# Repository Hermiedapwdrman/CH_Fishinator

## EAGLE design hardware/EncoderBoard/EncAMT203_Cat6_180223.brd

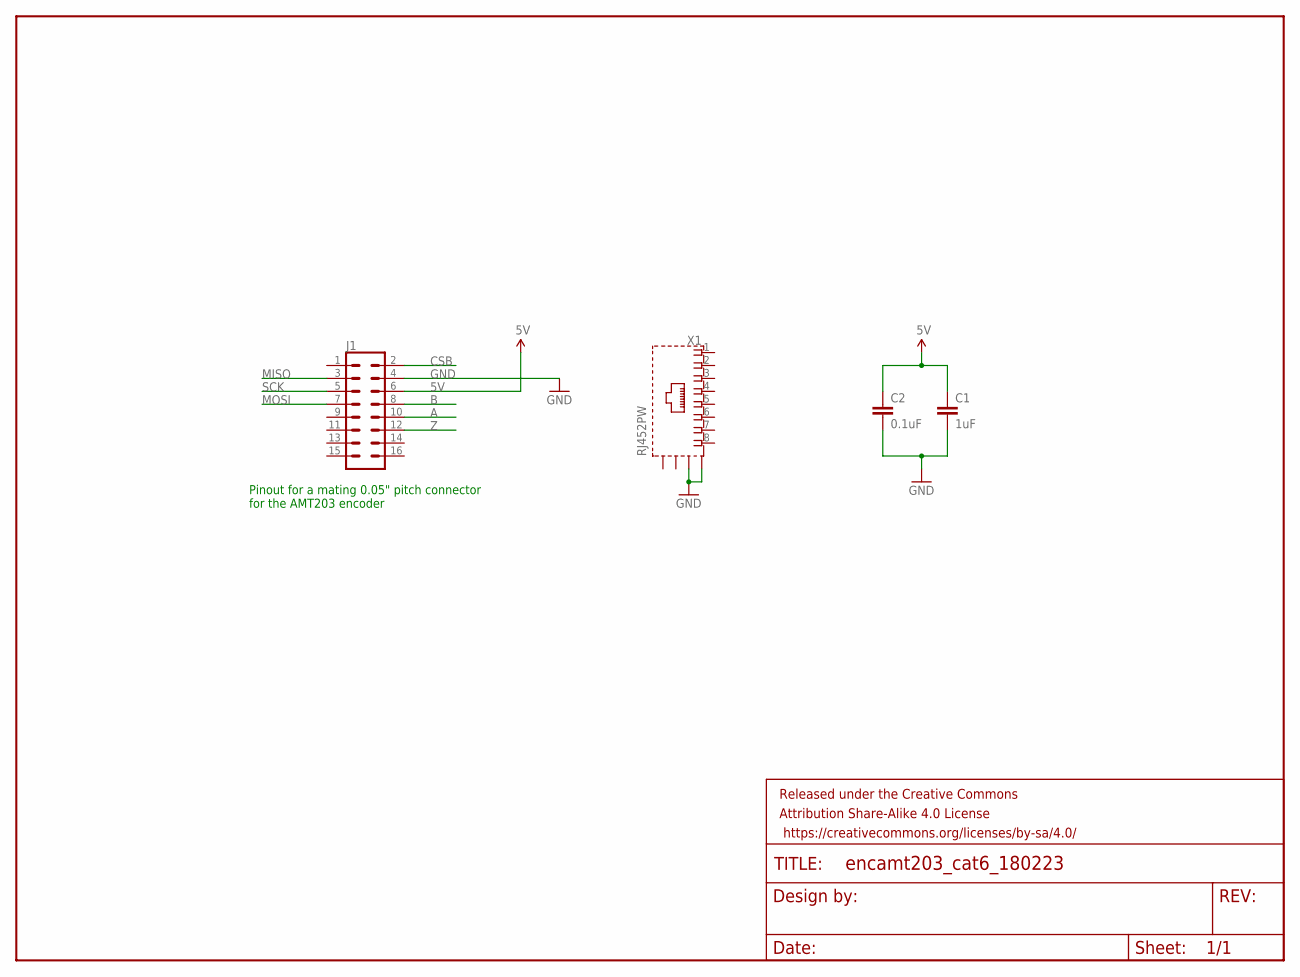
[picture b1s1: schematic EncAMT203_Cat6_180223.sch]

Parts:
C1: 1uF; 0603
C2: 0.1uF; 0603
FRAME1: FRAME-LETTERNO_PACKAGE; DUMMY
J1: CONN_08X2_1.27MM; 2X08_1.27MM
X1: RJ452PW; RJ45-SHIELD1

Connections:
5V: C1.1, C2.1, J1.6
A: J1.10
B: J1.8
CSB: J1.2
GND: C1.2, C2.2, J1.4, X1.S1 (S), X1.S2 (S)
MISO: J1.3
MOSI: J1.7
SCK: J1.5
Z: J1.12

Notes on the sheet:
Pinout for a mating 0.05" pitch connector for the AMT203 encoder

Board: 2 copper layers, 5 parts (3 on the bottom side), 2 nets, no tracks yet.

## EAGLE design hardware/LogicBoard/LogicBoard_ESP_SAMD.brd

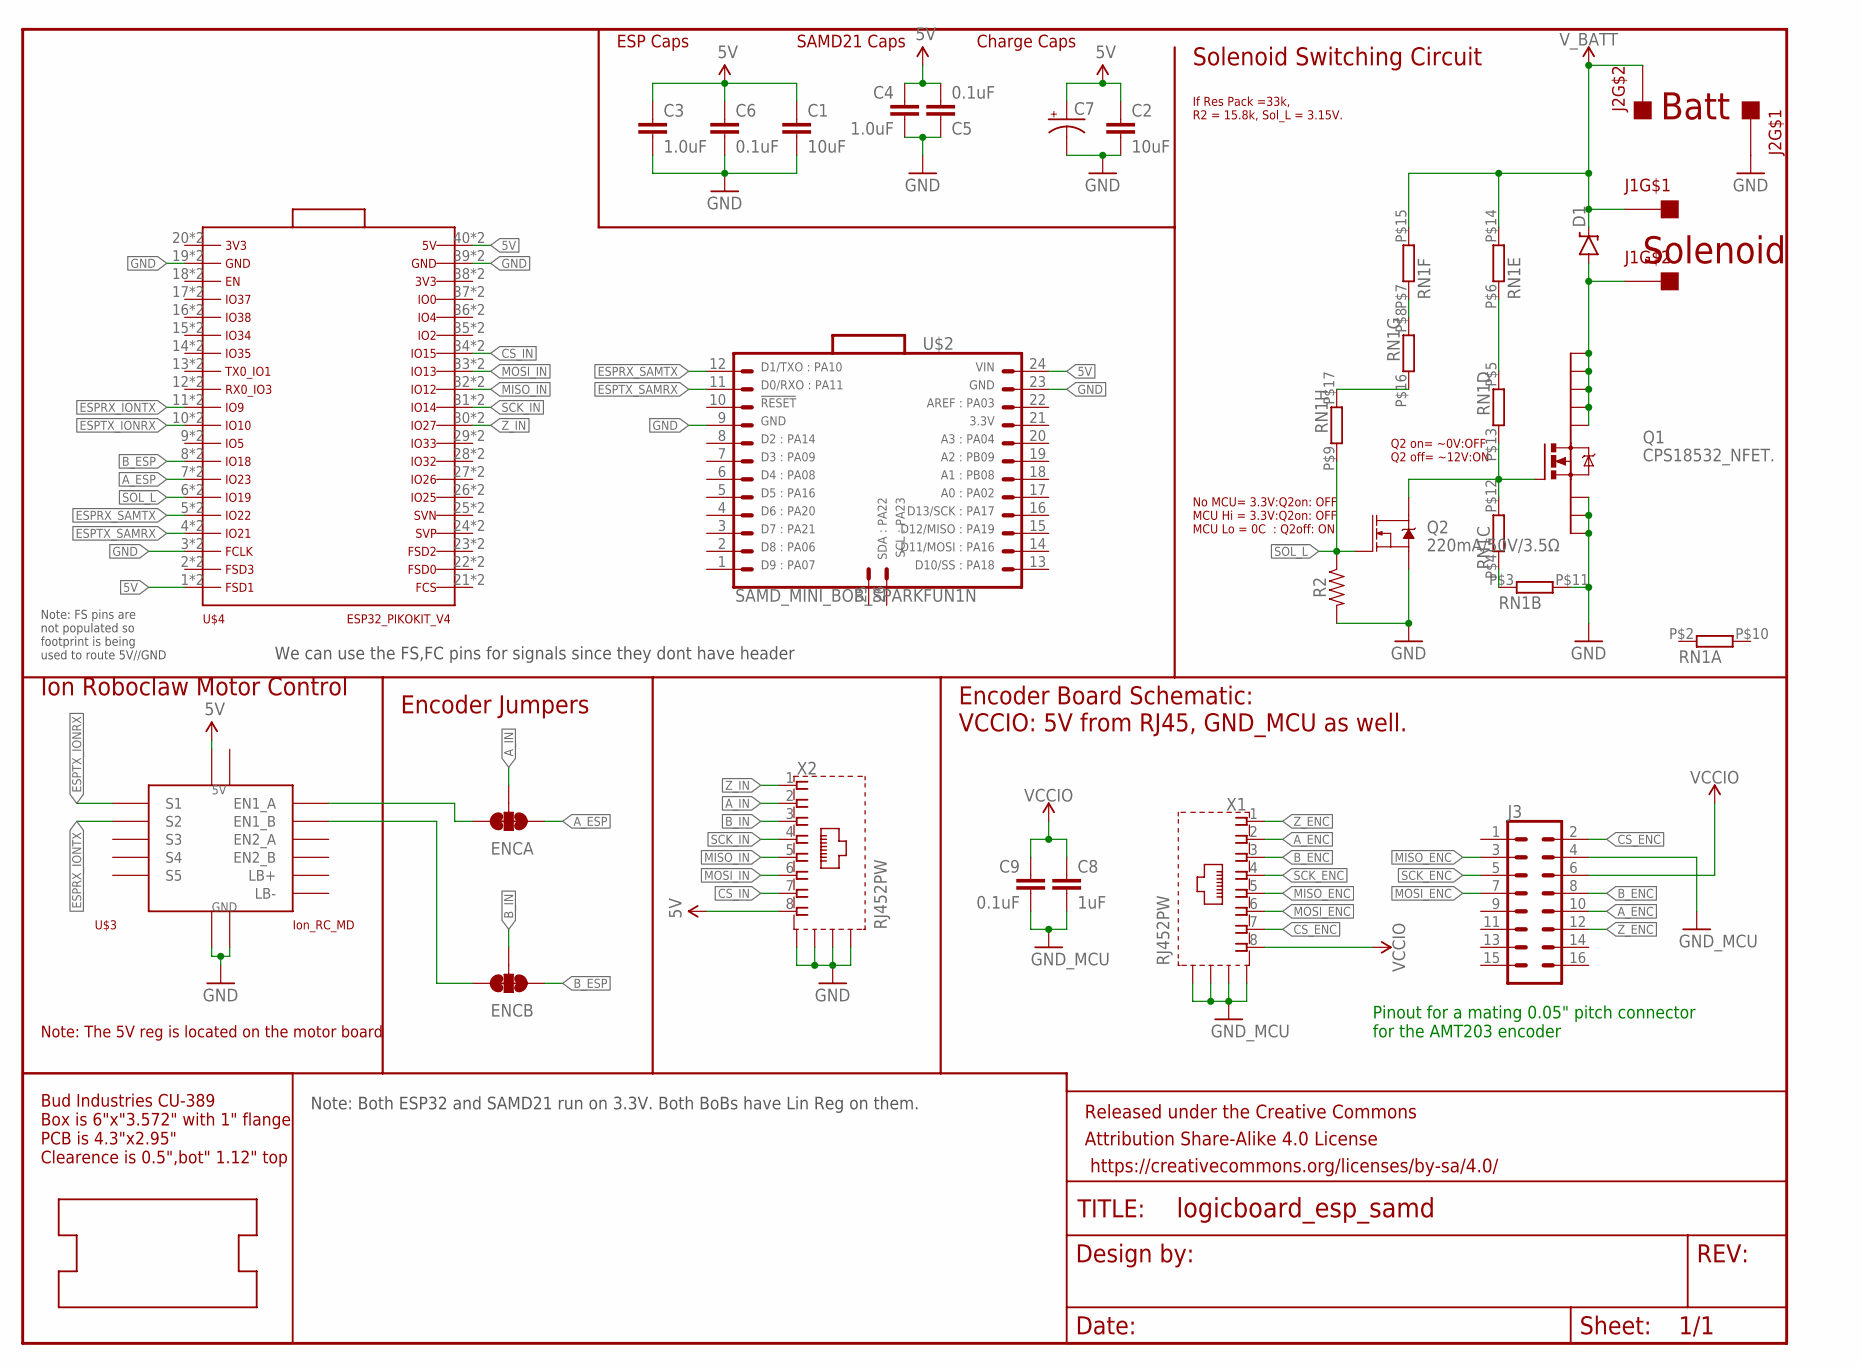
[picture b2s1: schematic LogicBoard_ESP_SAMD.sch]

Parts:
C1, C2: 10uF; 1206
C3, C4: 1.0uF; 0603
C5, C6, C9: 0.1uF; 0603
C7: CAP_POLPTH4; CPOL-RADIAL-1000UF-25V
C8: 1uF; 0603
D1: DIODE-SHOTKEY_SOD-123; SOD-123_MINI-SMA
ENCA: JUMPER-SMT_3_2-NC_TRACE_SILK; SMT-JUMPER_3_2-NC_TRACE_SILK
ENCB: JUMPER-SMT_3_2-NC_TRACE_SILK; SMT-JUMPER_3_2-NC_TRACE_SILK
FRAME1: FRAME-LETTERNO_PACKAGE; DUMMY
J1, J2: M2_TERMINAL_0200SPACING; M2_0200
J3: CONN_08X2_1.27MM; 2X08_1.27MM
Q1: CPS18532_NFET.; CSD18532_NFET_NEXTFET
Q2: 220mA/50V/3.5Ω; SOT23-3
R2: 0603
RN1: RESISTOR-DIL_8R-N742C163; RESISTOR-DIL_742C163
U$1: BOX_BUDIND_CU389STENCIL; BOX_BUDIND_CU389_STENCIL
U$2: SAMD_MINI_BOB_SPARKFUN1N; SAMD_MINI_BOB_SF_NOLABEL
U$3: ION_ROBOCLAW_MOTORDRVTOPVIEW; ION_ROBOCLAW_MOTORCNTL
U$4: ESP32_PICOKIT_V42N; ESP32_PICOKIT_2N
X1, X2: RJ452PW; RJ45-SHIELD1

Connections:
5V: C1.1, C2.1, C3.1, C4.1, C5.2, C6.1, C7.1 (+), U$2.24 (VIN), U$3.5V@1 (5V), U$3.5V@2 (5V), U$3.5V@3 (5V), U$3.5V@4 (5V), U$3.5V@5 (5V), U$4.1, U$4.40, U$4.41, U$4.80, X2.8
!SOL_L!: Q2.1 (G), R2.1, RN1.P$9 (2), U$4.6, U$4.46
A_ENC: J3.10, X1.2
A_ESP: ENCA.1, U$4.7, U$4.47
A_IN: ENCA.2, X2.2
B_ENC: J3.8, X1.3
B_ESP: ENCB.1, U$4.8, U$4.48
B_IN: ENCB.2, X2.3
CS_ENC: J3.2, X1.7
CS_IN: U$4.34, U$4.74, X2.7
ESPRX_IONTX: U$3.S2, U$4.11, U$4.51
ESPRX_SAMTX: U$2.12 (D1), U$4.5, U$4.45
ESPTX_IONRX: U$3.S1, U$4.10, U$4.50
ESPTX_SAMRX: U$2.11 (D0), U$4.4, U$4.44
GND: C1.2, C2.2, C3.2, C4.2, C5.1, C6.2, C7.2 (-), J2.P$2, Q1.P$1 (S1), Q1.P$2 (S2), Q1.P$3 (S3), Q2.2 (S), R2.2, RN1.P$11 (2), U$2.9 (GND), U$2.23 (GND), U$3.GND@1 (GND), U$3.GND@2 (GND), U$3.GND@3 (GND), U$3.GND@4 (GND), U$3.GND@5 (GND), U$3.GND@6 (GND), U$3.GND@7 (GND), U$4.3, U$4.19, U$4.39, U$4.43, U$4.59, U$4.79, X2.S1 (S), X2.S2 (S), X2.S3 (S), X2.S4 (S)
GND_MCU: C8.2, C9.2, J3.4, X1.S1 (S), X1.S2 (S), X1.S3 (S), X1.S4 (S)
MISO_ENC: J3.3, X1.5
MISO_IN: U$4.32, U$4.72, X2.5
MOSI_ENC: J3.7, X1.6
MOSI_IN: U$4.33, U$4.73, X2.6
unnamed: D1.A, J1.P$3, Q1.P$5 (D1), Q1.P$6 (D2), Q1.P$7 (D3), Q1.P$8 (D4), Q1.P$9 (D_PAD)
unnamed: RN1.P$3 (1), RN1.P$4 (1)
unnamed: Q1.P$4 (G), Q2.3 (D), RN1.P$12 (2), RN1.P$13 (2)
unnamed: RN1.P$7 (1), RN1.P$8 (1)
unnamed: RN1.P$16 (2), RN1.P$17 (1)
unnamed: RN1.P$5 (1), RN1.P$6 (1)
unnamed: ENCB.3, U$3.EN1_B
unnamed: ENCA.3, U$3.EN1_A
SCK_ENC: J3.5, X1.4
SCK_IN: U$4.31, U$4.71, X2.4
VCCIO: C8.1, C9.1, J3.6, X1.8
V_BATT: D1.C, J1.P$2, J2.P$3, RN1.P$14 (2), RN1.P$15 (2)
Z_ENC: J3.12, X1.1
Z_IN: U$4.30, U$4.70, X2.1

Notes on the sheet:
Note: Both ESP32 and SAMD21 run on 3.3V. Both BoBs have Lin Reg on them.
We can use the FS,FC pins for signals since they dont have header
Pinout for a mating 0.05" pitch connector for the AMT203 encoder
Encoder Board Schematic: VCCIO: 5V from RJ45, GND_MCU as well.
If Res Pack =33k, R2 = 15.8k, Sol_L = 3.15V.
Encoder Jumpers
Ion Roboclaw Motor Control
Note: The 5V reg is located on the motor board
Solenoid Switching Circuit
Solenoid
Batt
Q2 on= ~0V:OFF Q2 off= ~12V:ON
No MCU= 3.3V:Q2on: OFF MCU Hi = 3.3V:Q2on: OFF MCU Lo = 0C : Q2off: ON
ESP Caps
SAMD21 Caps
Charge Caps
Note: FS pins are not populated so footprint is being used to route 5V//GND

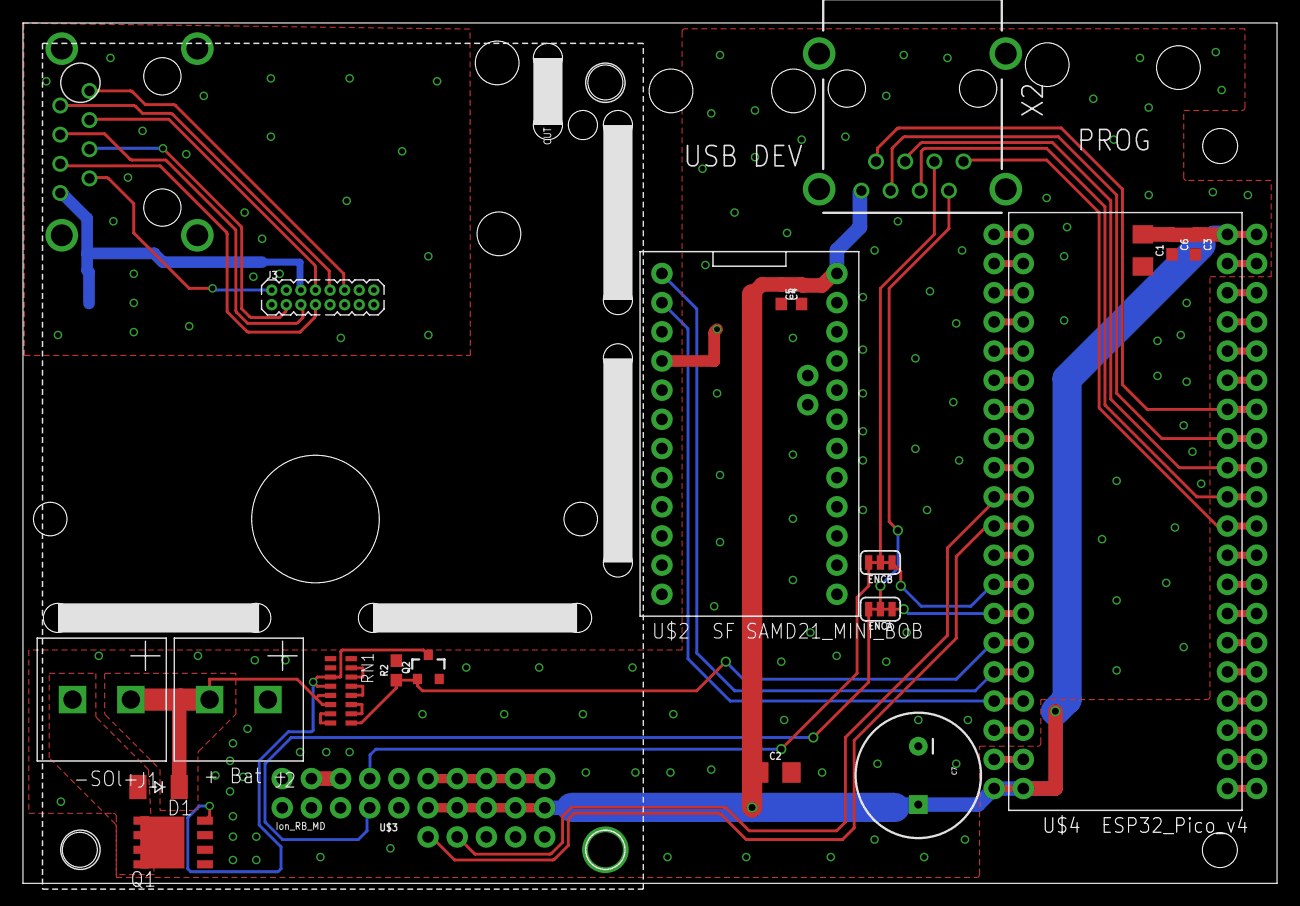
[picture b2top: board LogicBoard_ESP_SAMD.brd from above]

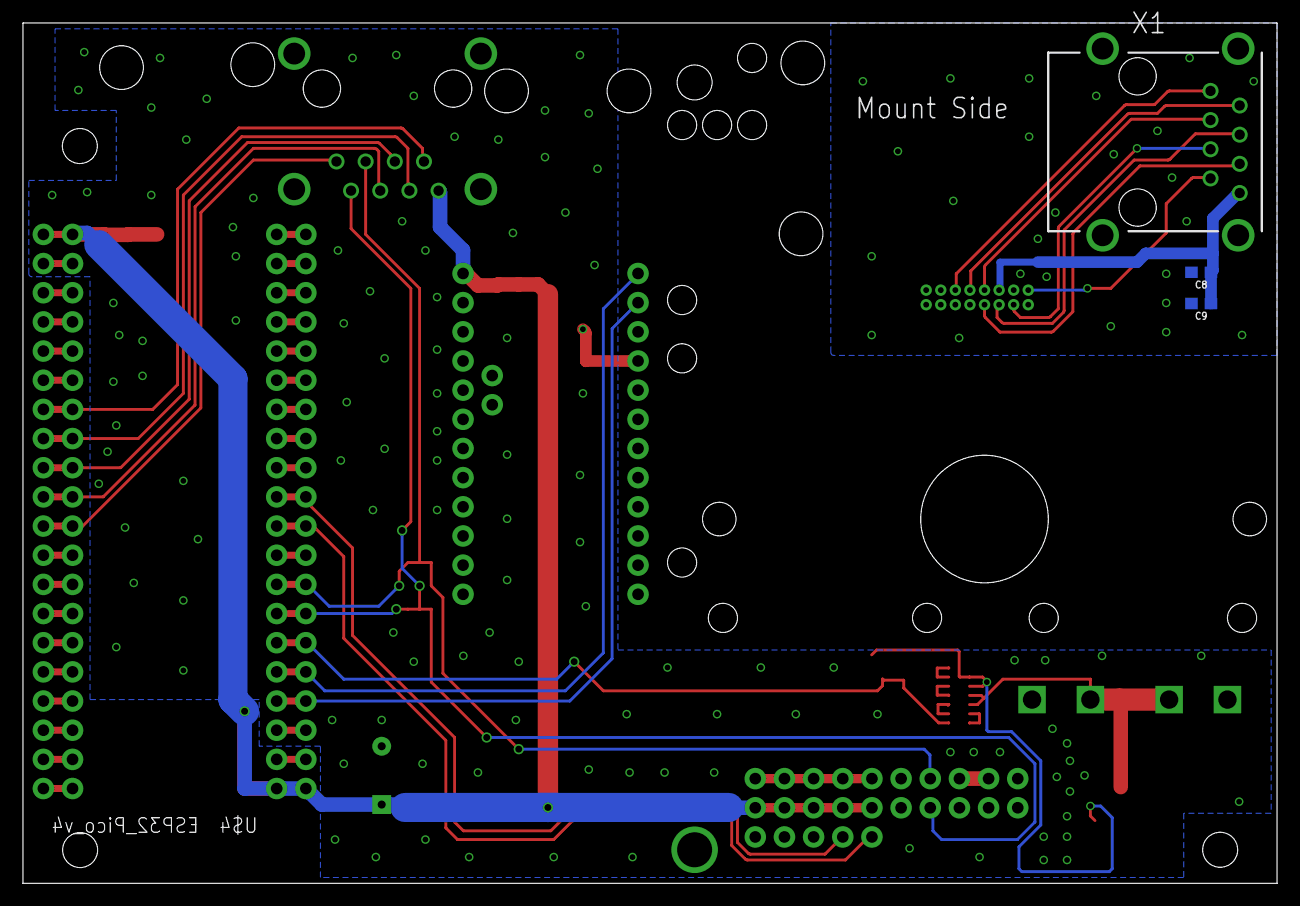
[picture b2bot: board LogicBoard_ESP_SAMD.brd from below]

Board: 2 copper layers, 109.2 x 74.9 mm, 27 parts (3 on the bottom side), 34 nets.

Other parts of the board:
FRAME2: FRAME-LETTERNO_PACKAGE; DUMMY

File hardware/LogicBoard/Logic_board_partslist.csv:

Partlist

Exported from LogicBoard_ESP_SAMD.sch at 3/12/18 10:39 AM

EAGLE Version 7.7.0 Copyright (c) 1988-2016 CadSoft

Assembly variant: 

Part     Value                        Device                       Package                      Library               Sheet

C1       10uF                         10UF-1206-6.3V-20%           1206                         SparkFun-Capacitors   1
C2       10uF                         10UF-1206-6.3V-20%           1206                         SparkFun-Capacitors   1
C3       1.0uF                        1.0UF-0603-16V-10%-X7R       0603                         SparkFun-Capacitors   1
C4       1.0uF                        1.0UF-0603-16V-10%-X7R       0603                         SparkFun-Capacitors   1
C5       0.1uF                        0.1UF-0603-25V-5%            0603                         SparkFun-Capacitors   1
C6       0.1uF                        0.1UF-0603-25V-5%            0603                         SparkFun-Capacitors   1
C7                                    CAP_POLPTH4                  CPOL-RADIAL-1000UF-25V       !!Pat_030112          1
C8       1uF                          0.1UF-0603-25V-5%            0603                         SparkFun-Capacitors   1
C9       0.1uF                        0.1UF-0603-25V-5%            0603                         SparkFun-Capacitors   1
D1       DIODE-SHOTKEY_SOD-123        DIODE-SHOTKEY_SOD-123        SOD-123_MINI-SMA             !!Pat_030112          1
ENCA     JUMPER-SMT_3_2-NC_TRACE_SILK JUMPER-SMT_3_2-NC_TRACE_SILK SMT-JUMPER_3_2-NC_TRACE_SILK SparkFun-Jumpers      1
ENCB     JUMPER-SMT_3_2-NC_TRACE_SILK JUMPER-SMT_3_2-NC_TRACE_SILK SMT-JUMPER_3_2-NC_TRACE_SILK SparkFun-Jumpers      1
J1       M2_TERMINAL_0200SPACING      M2_TERMINAL_0200SPACING      M2_0200                      !!Pat_030112          1
J2       M2_TERMINAL_0200SPACING      M2_TERMINAL_0200SPACING      M2_0200                      !!Pat_030112          1
J3                                    CONN_08X2_1.27MM             2X08_1.27MM                  !!Pat_030112          1
Q1       CPS18532_NFET.               CPS18532_NFET.               CSD18532_NFET_NEXTFET        !!Pat_030112          1
Q2       220mA/50V/3.5?               MOSFET-NCH-BSS138            SOT23-3                      SparkFun-DiscreteSemi 1
R2                                    RESISTOR0603                 0603                         SparkFun-Resistors    1
RN1                                   RESISTOR-DIL_8R-N742C163     RESISTOR-DIL_742C163         !!Pat_030112          1
U$2      SAMD_MINI_BOB_SPARKFUN1N     SAMD_MINI_BOB_SPARKFUN1N     SAMD_MINI_BOB_SF_NOLABEL     !!Pat_030112          1
U$3      ION_ROBOCLAW_MOTORDRVTOPVIEW ION_ROBOCLAW_MOTORDRVTOPVIEW ION_ROBOCLAW_MOTORCNTL       PW_CH_personal        1
U$4      ESP32_PICOKIT_V42N           ESP32_PICOKIT_V42N           ESP32_PICOKIT_2N             PW_CH_personal        1
X1       RJ452PW                      RJ452PW                      RJ45-SHIELD1                 PW_CH_personal        1
X2       RJ452PW                      RJ452PW                      RJ45-SHIELD1                 PW_CH_personal        1

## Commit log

2017-11-01 Initial commit for a combined LUFA/AT90 and ESP32 MCU project.
2017-11-01 Tested build for ESP32 files, it works.
2017-11-01 Updated esp32 git ignore.
2017-11-01 Tested Lufa firmware, built successfully. Added lufa gitignore.
2017-11-01 Removed zombie files for IDE and .ignore
2017-11-01 Removing IDE files not needing tracking.
2017-11-13 Updated components to reflect the ESP template library.
2017-11-15 Updated documentation added resources.
2017-11-15 Clarified project names, and updated sdkconfig UART settings to run at 921600 for everthing!
2017-12-13 New initial commit: Using git submodules to track sdk versions and make code more'complete'
2017-12-13 Updated cmake indexer includes for esp-idf 3.0rc1 and updated readme's
2017-12-13 Updated readmes to reflect new directory and project organization.
2017-12-13 Modified esp-idf to v3.0 branch/release
2017-12-20 Updated readme for submodules
2017-12-20 Updated .gitignore to not include clion directory.
2017-12-20 Changed paths to local git repos of big esp32 sdks
2017-12-20 Updated paths and readme, compiles just fine.
2017-12-20 updated readme regarding submodules
2017-12-20 Initial Commit for CH_Fishinator
2017-12-20 Updated readmes and cmakelists for project name.
2017-12-20 Updated lufa clion project cmake for better project name.
2018-01-08 Updated component readme, and sdk config for esp-idf v3.0-rc1
2018-01-08 Updated configs and updated submodules to track certain maintainable branches
2018-01-09 Added raw motor_vpid code into project, added arduino pid library as component submodule.
2018-01-09 Updated build files, esp config and renamed main file.
2018-01-12 Updating submodules
2018-01-12 Updating submodules, moved VPID and Pid to its own library
2018-01-12 Fixed cmake indexer includes, commented out LOTS of non portable code: NEEDS TO BE FIXED
2018-01-12 Update submodule
2018-01-12 Toolchain, and submodules setup, and building, non portable code in CHMotordriver, and main source are commented out. Now port can begin
2018-01-22 Updated arduino to master branch and FF to current
2018-01-22 Updated edp-idf to newest, compaitble with arduino
2018-01-22 Updated component readme, and sdk config for esp-idf v3.1 -rc1
2018-01-22 Updated arduino sdk
2018-01-22 Updated submodule readme
2018-01-22 Update sdkconfig for C++ exceptions.
2018-01-22 Updated readme, and sdkconfig for new esp-idf commits.
2018-01-29 Updated submodules
2018-01-29 Update readme and esp-idf submodule
2018-02-01 Udated espidf submodule
2018-02-01 Changed default port to ttyUSB0
2018-02-02 Updated cmake idf includes for components drivers, changed and test built idf syntax with arduino as component.
2018-02-02 Updated readme to note which project folders should be marked as source for indexing.
2018-02-07 Added Roboclaw and AMT20 libraries, fast forwarded espidf
2018-02-07 Fast forwarded roboclaw library
2018-02-07 Merge remote-tracking branch 'template_local/master' into Motor_VPID_Integration
    # Conflicts:
    # firmware/esp_src/ReadMe_Components.md
    # firmware/esp_src/components/esp-idf
    # firmware/esp_src/sdkconfig.old
2018-02-07 Roughed out case statement for testing casting.
2018-02-08 Diactivated arduino init, working peripherial commands for test. Solenoid, reel, move cast location. no working implementaion of rod motor.
2018-02-08 Working encoder implementation (CAUTION has gone strange before.), getchar and other peripherials.
2018-02-08 WORKING fast and slow position calls from function. Still wary of comm.
2018-02-09 Updated AMT20Encoder set zero, not variable need to be passed.
    Updated control functions, added zero console command, aded some delays which might gbe removed eventually.
2018-02-09 Moved encoder isr to main function due to solenoid handling. Added cast sequence to main casting function. Made rtos tick at 1000hz, not sure if its needed though
2018-02-14 Adjusted the casting sequence and some of the movement parameters
2018-02-14 More adjustments on casting parameters, sped up slow move a bit. I am impatient.
2018-02-14 Added timing and speed measurement calls for future tuning.
2018-02-21 Added ESP32 snippets as base library to the template, good examples and utils.
2018-02-21 updated readme and some build flags.
2018-02-22 updated readmes and comments aboud sdkconfig.h
2018-02-22 Added note to readme about init commit, added myMain in c++ called from app_main wrapper
2018-02-27 Added atmel samd21 firmware folder, configured with platformio.
2018-02-27 Copied over usb descripter example from arduino sam library. Compiles
2018-02-27 Added exp to find serial ports, SerialUSB for usb device comm, Serial 1 for breakout on board.
2018-02-27 Replaceds seraial monitor macro with hardware port(ser1), which is broken out on sf board
2018-02-27 Started working on circuit and hardware design, included datasheets
2018-02-27 Copied both examples with some comments. TODO: Reame for samd
2018-02-27 Updated name in Cmakelists
2018-02-27 Updated samd name and added usb comm descriptors
2018-02-27 Working communication between samd on serial1 and esp on uart2!
2018-02-27 Using test code for usb desc, will read a usb device on startu succesfully.
2018-02-28 Adjust esp read code,(need to switch to idf buffer), test descripter reads successfully.
2018-02-28 Move uart comm on esp to espidf function calls, better control.
2018-03-09 Added hardware (eagle) sch and brd files
2018-03-26 Updated pinouts for fishing rod beta 2. Updated sdk versions, carried forward firmware docs.
2018-03-26 Modified VPID settings, updated sdkconfig with new sdk options.
2018-03-26 Fishing state machine is replicated and seems to be working.
2018-03-26 Updated vars and included control document.
2018-03-27 Started cleaning up code, added fish prompts and printouts for layman use.
2018-03-27 Updated terminal help printout, and some info printouts for state machine, added emergency stop.
2018-03-27 Added kludgy decay timers for smoother reel and rod manual control. Added user methods for setting positions, and other methods. Some reset checks
2018-03-27 Added date rev, fixed some prompts.
2018-03-27 Fixed typos, added splash and changed function a bit.
2018-03-29 Added a few extra control cases to the state machine, user interface.
2018-03-30 Fixed some ui keymaps; state debouncing to prevent changings states too fast.
2018-03-30 Udated sdks repos, update readme
2018-03-30 Changed clion git status.
2018-03-30 Deleted submodlue esp snippits
2018-03-30 Minor fix on casting location check, updated sdk config.
2018-03-30 Bump build ver.
2018-04-02 Cleaned up folder structure.
2018-04-02 update submodules
2018-04-03 Updated esp_err string function, which seems to be awol.
2018-04-04 Updated code template and began refactoring procedure.
2018-04-05 Moved vars, init, isr example from main to AMT20 library, now portable.
2018-04-05 Moved fishing Command and communication variable to their own files.
2018-04-06 Updated code documentation, cleaned up a bit
2018-04-06 Update state machine, switched case nesting to state(trasistion)
2018-04-06 bump patch version
2018-04-06 Revert "cleaning up old branches"

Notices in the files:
parts and their libraries:
SparkFun-Capacitors: Licensing: Creative Commons ShareAlike 4.0 International - https://creativecommons.org/licenses/by-sa/4.0
SparkFun-Aesthetics: Released under the Creative Commons Attribution Share-Alike 4.0 License
SparkFun-Aesthetics: https://creativecommons.org/licenses/by-sa/4.0
